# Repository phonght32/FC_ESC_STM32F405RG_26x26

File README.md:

# FC_ESC_STM32F405RG_26x26

### 1. Overview

All-in-One (AIO) circuit for quadcopter. STM32F405 is the main controller for FC and EFM8BB21 is the main controller for ESC. Screw hole dimension is 26x26 mm that compatible for almost tiny drone frame. 

Everything about this board: Schematic, PCB gerber and BOM are free to distribute under open-source license for users.

### 2. Specifications

| Items               | Specifications                                               |
| ------------------- | ------------------------------------------------------------ |
| Power supply        | Pin LiPo 2-4 cell                                            |
| Microcontroller     | STM32F405RGT6 / 32-bit ARM Cortex-M4 with FPU(168MHz, 225DMIPS) |
| Sensors             | MPU6000 (3 axis gyroscope, 3 axis accelerometer) <br />BMP280 (barometer)<br />INA186 (current) |
| Programmer          | JTAG/SWD connector                                           |
| Communicaton Ports  | UART x 4<br />I2C x 1<br />SPI x 1                           |
| OSD                 | Built-in AT7456                                              |
| LEDs and Buttons    | LED RED: 3V3 power on<br />LED BLUE: User status             |
| Output power source | TPS5430 5V@5A<br />RT9013 3V3@500mA                          |
| Dimensions          | 34 x34 mm<br />Screw hole 26 x 26 mm                         |

**NOTE:**

This board use jumper to select 5V power source and to enable 3V3 power supply.

### 3. Layout / Pin map

| Function    | Pin                                                          |
| ----------- | ------------------------------------------------------------ |
| UART1       | PA9: TX<br />PA10: RX                                        |
| UART3       | PB10: TX<br />PB11: RX                                       |
| UART4       | PA0: TX<br />PA1: RX                                         |
| UART6       | PC6: TX<br />PC7: RX                                         |
| SPI2        | PB12: CS<br />PB13: CLK<br />PB14: MISO<br />PB15: MOSI      |
| I2C2        | PB10: SCL<br />PB11: SDA                                     |
| LED         | LED status: PB7<br />LED strip: PB6                          |
| BUZZER      | PC13                                                         |
| USB Port    | D-: PA11<br />D+: PA12                                       |
| Measurement | Current sens: PC1<br />Voltage sens: PC2<br />USB voltage sens: PC5 |

### 4. Hardware design

#### Schematic

#### PCB F.Cu

#### PCB In1.Cu

#### PCB In2.Cu

#### PCB In3.Cu

#### PCB In4.Cu

#### PCB In5.Cu

#### PCB In6.Cu

#### PCB B.Cu

#### Dimension

#### 3D Top

#### 3D Bot

### 5. Bill of Materials (BOM)

[Download.](assets/BOM/FC_ESC_STM32F405RG_26x26.xlsx)

### 6. Gerber

[Download.](assets/gerber_FC_ESC_STM32F405RG_26x26_v1_0.zip)

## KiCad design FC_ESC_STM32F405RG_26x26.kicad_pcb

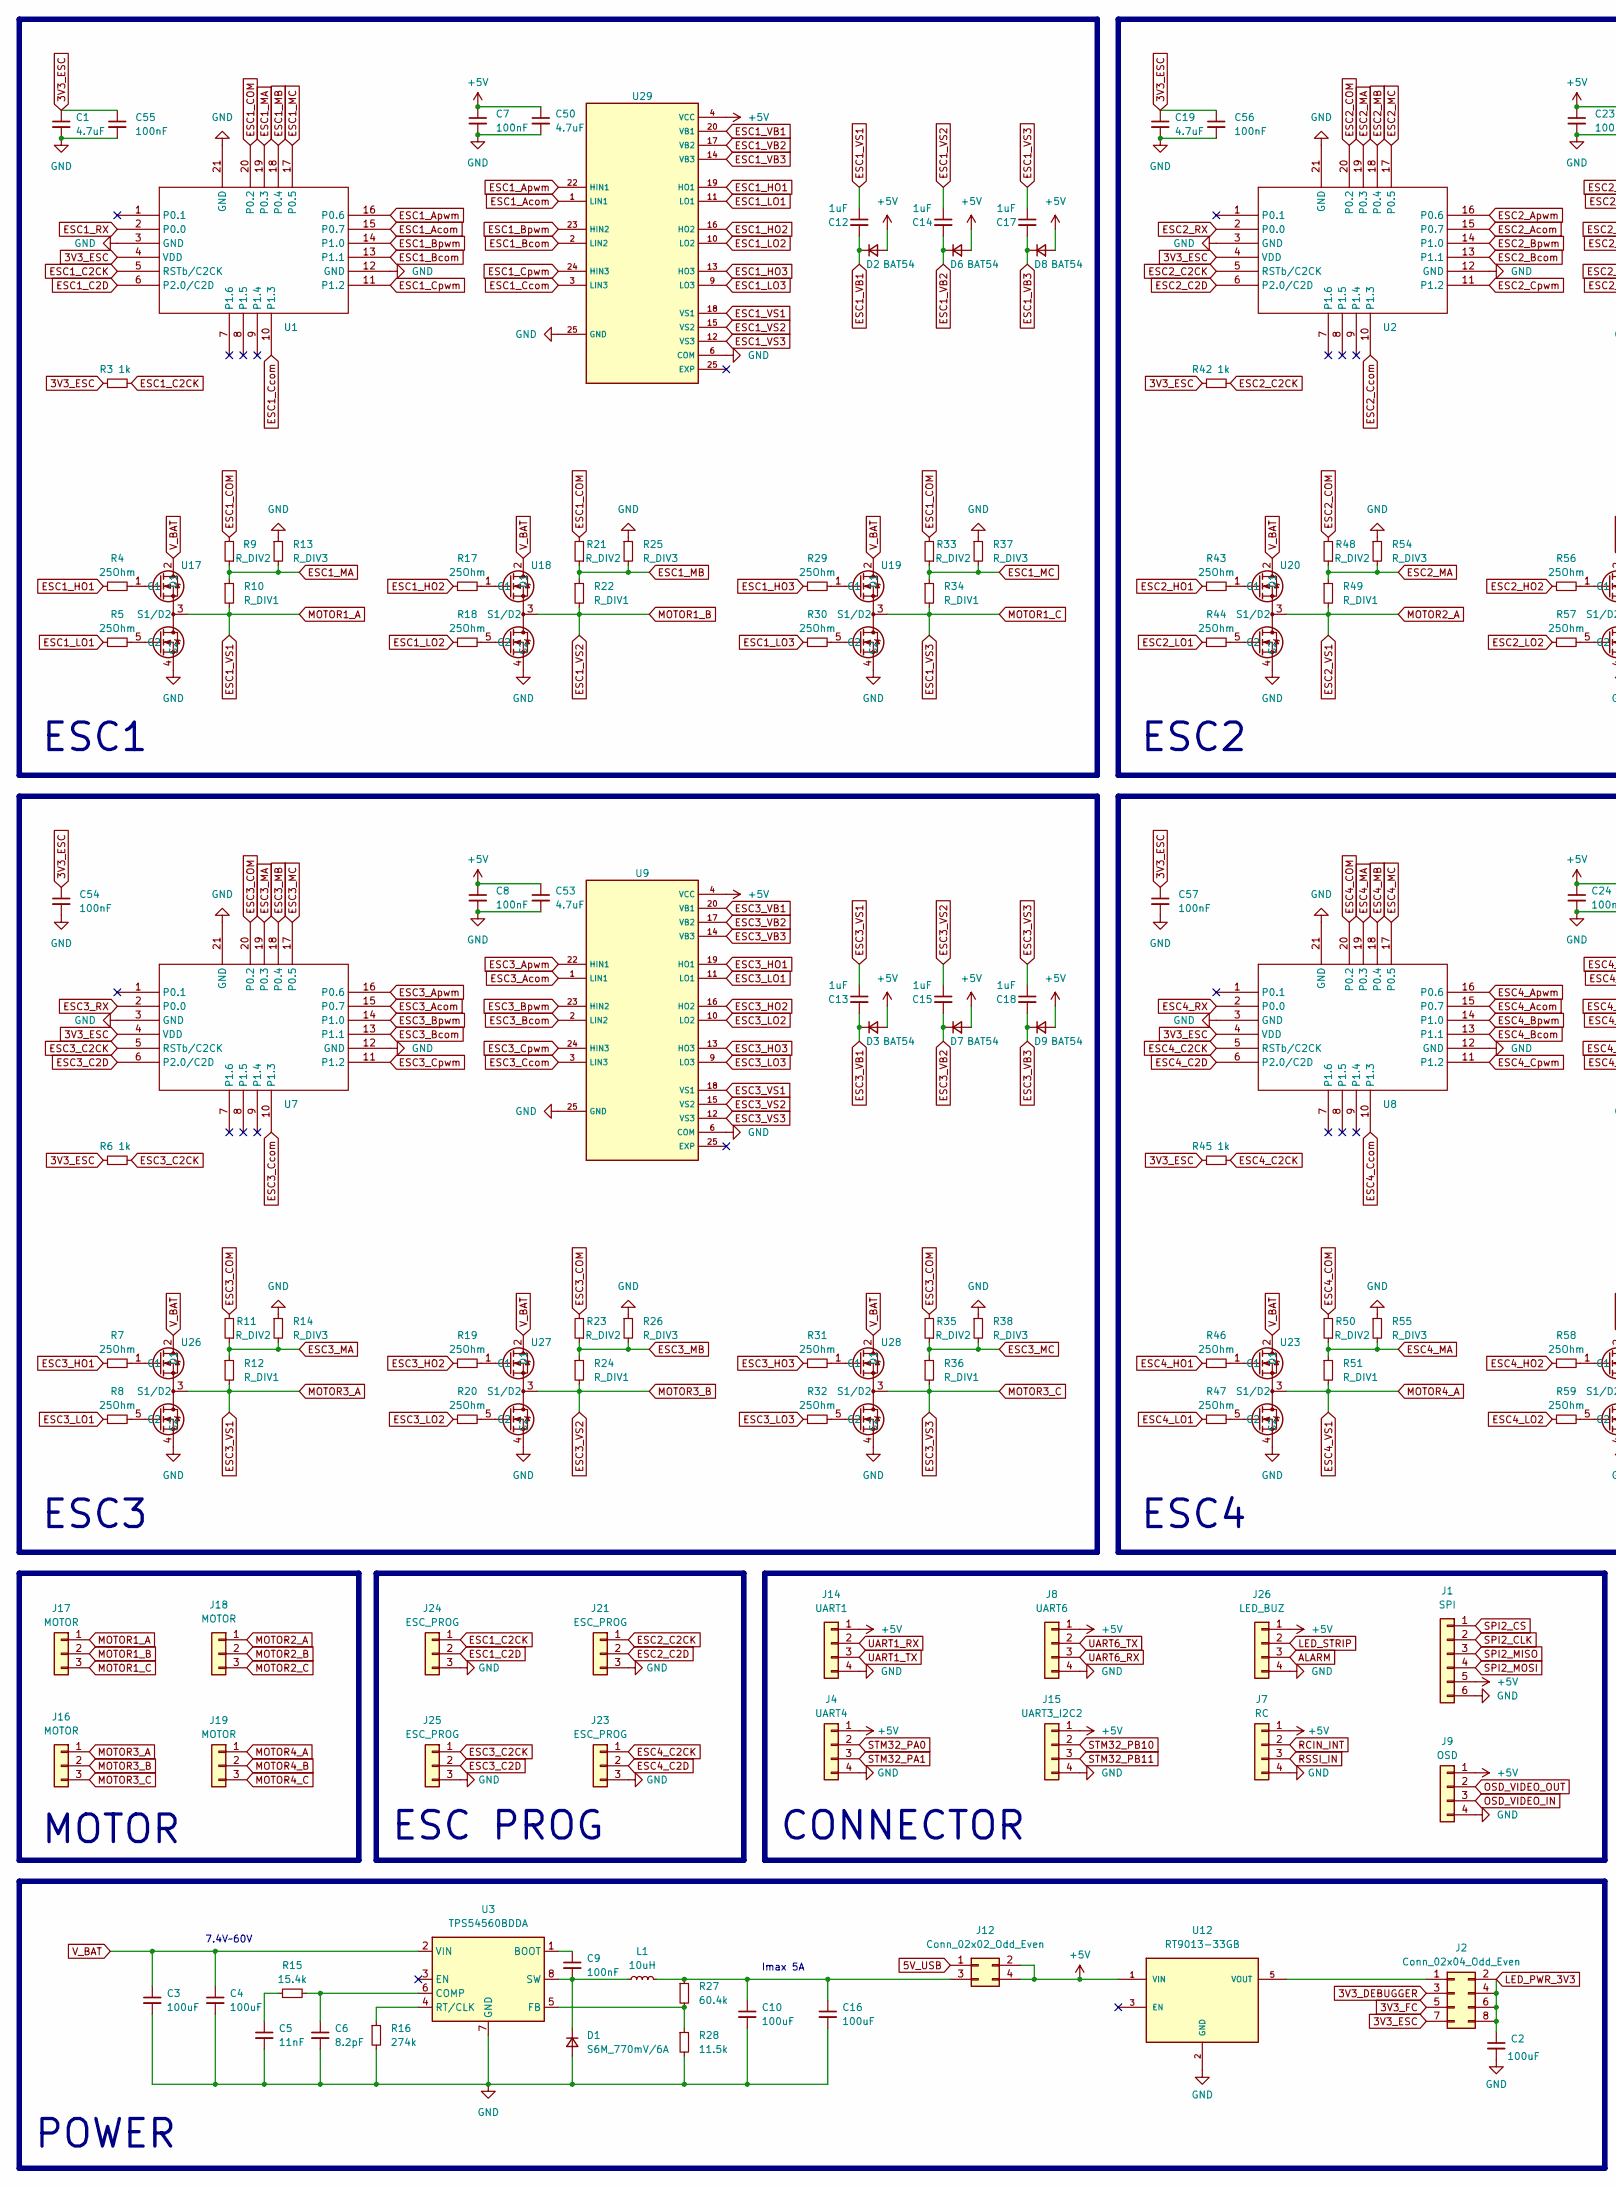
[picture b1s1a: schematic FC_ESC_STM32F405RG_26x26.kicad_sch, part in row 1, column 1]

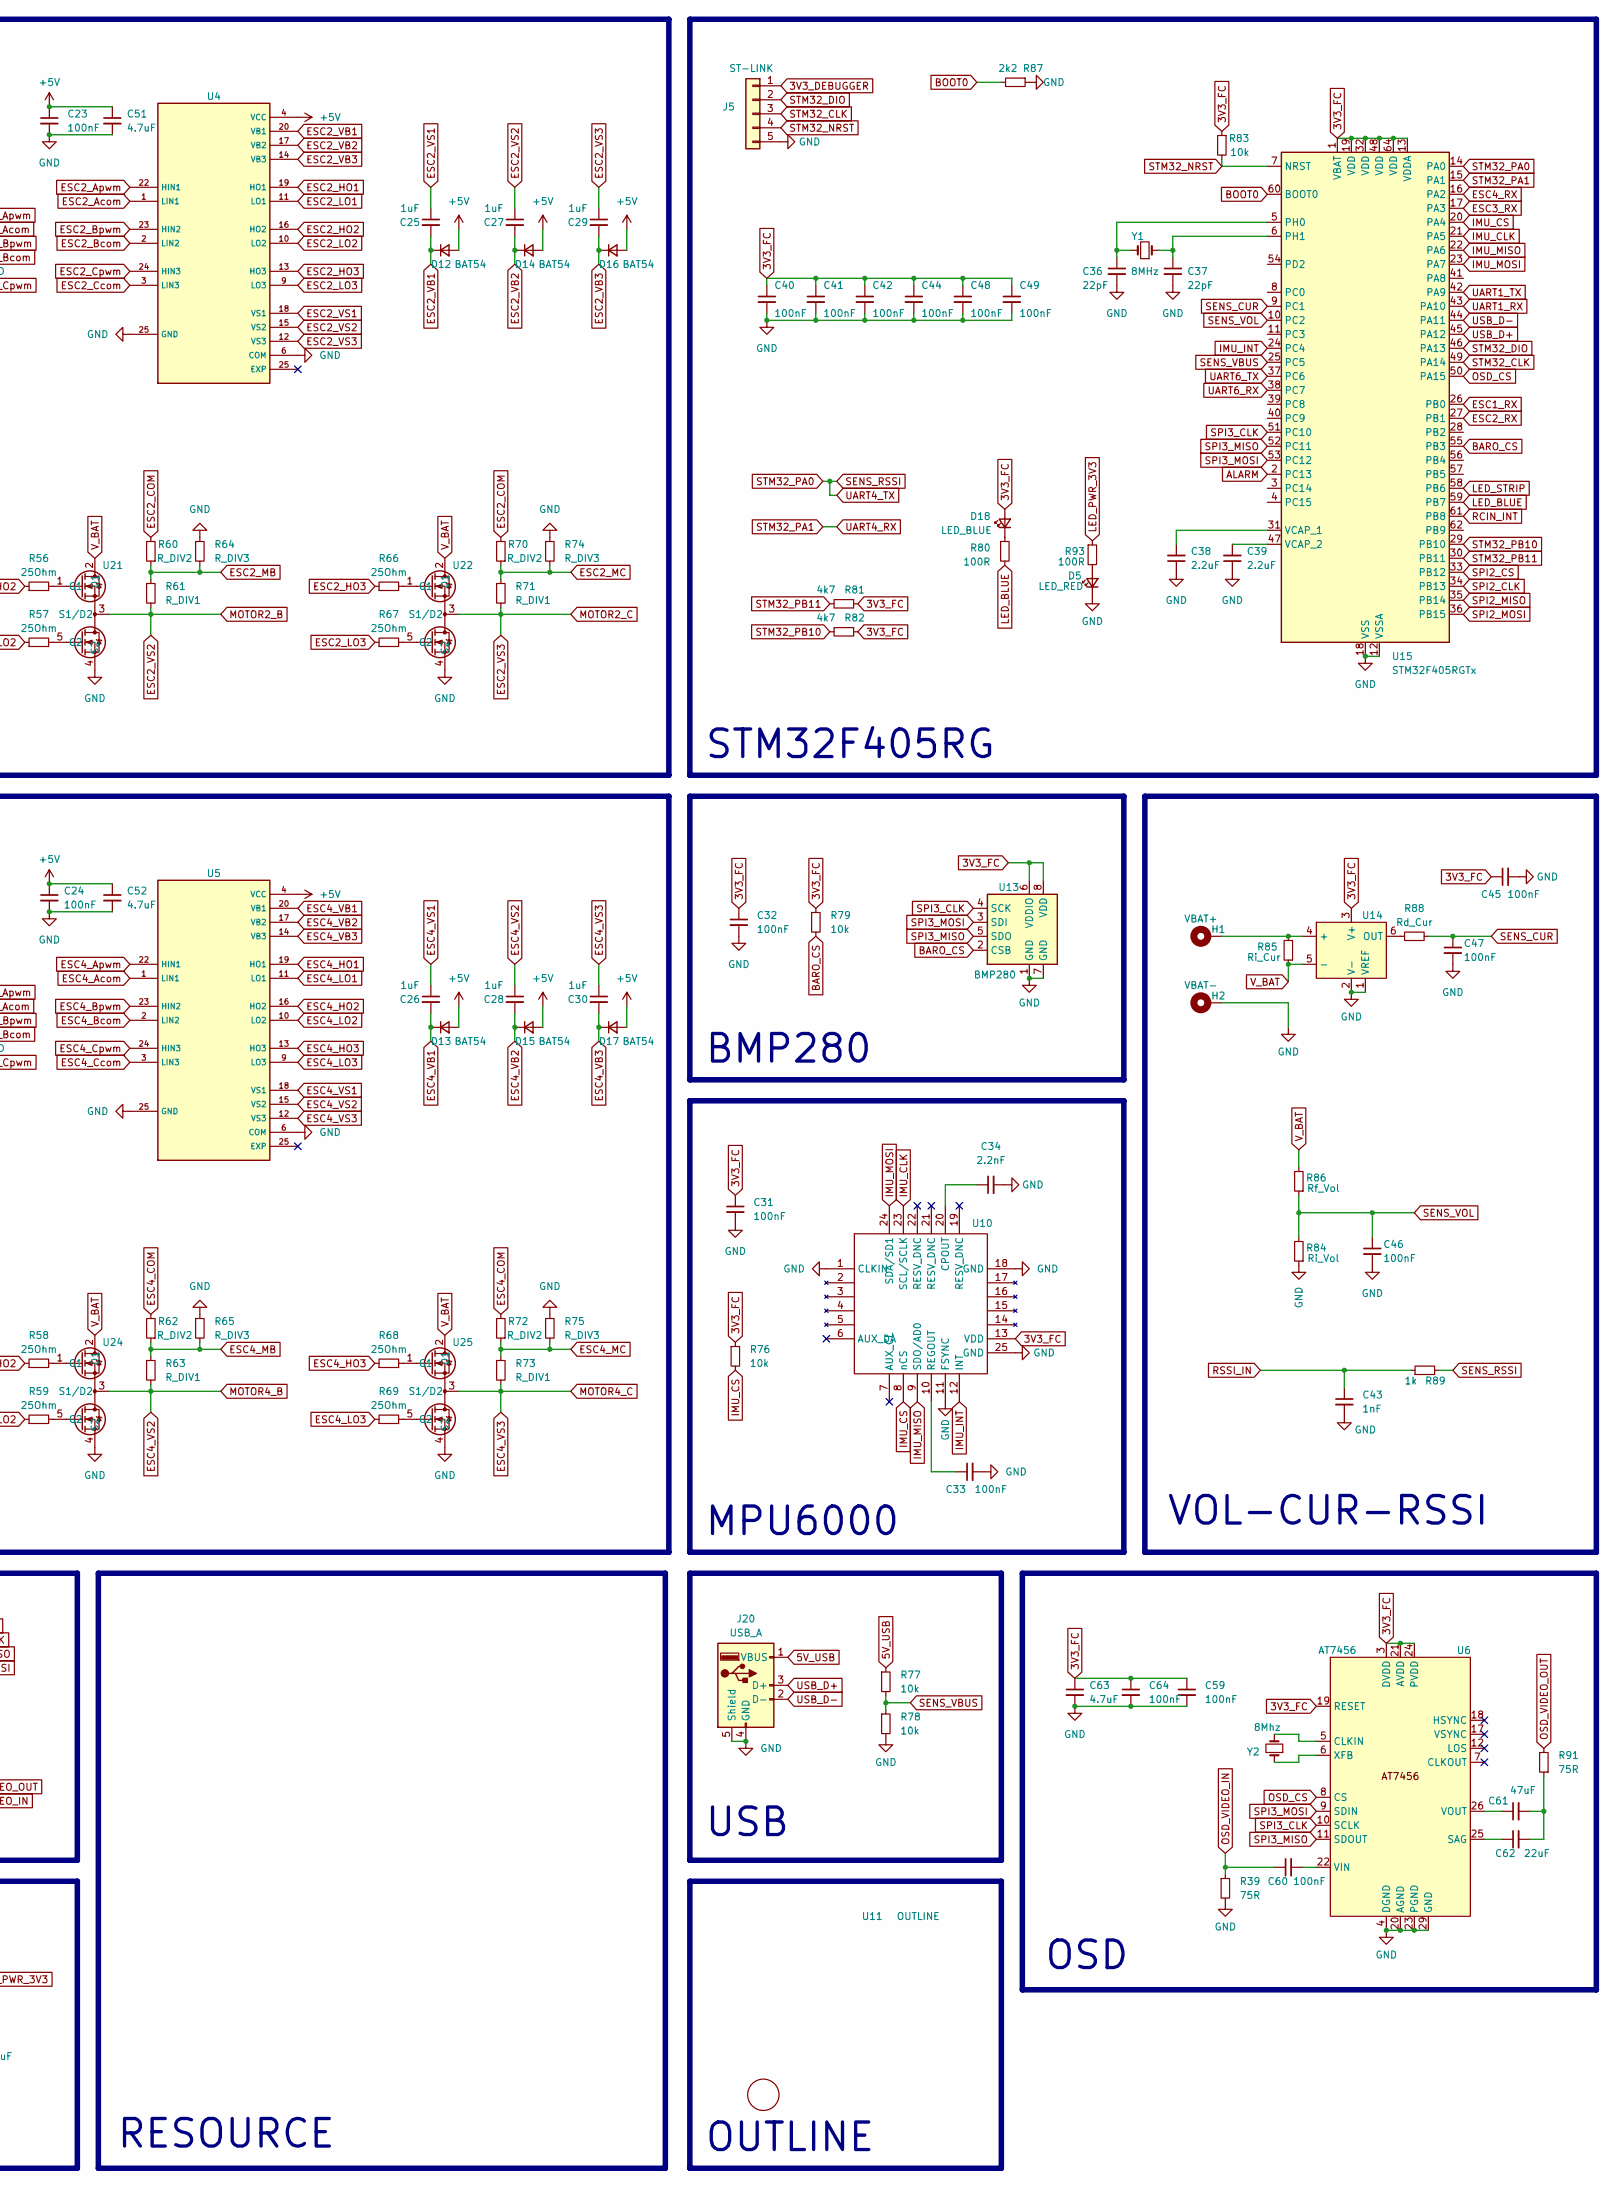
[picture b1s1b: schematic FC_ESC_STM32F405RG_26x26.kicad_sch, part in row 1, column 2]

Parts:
C1, C19: 4.7uF; C_1206_3216Metric_Pad1.33x1.80mm_HandSolder
C2, C3, C4, C10: 100uF; C_1210_3225Metric_Pad1.33x2.70mm_HandSolder
C5: 11nF; C_0402_1005Metric_Pad0.74x0.62mm_HandSolder
C6: 8.2pF; C_0402_1005Metric_Pad0.74x0.62mm_HandSolder
C7, C8, C9, C23, C24, C31, C32, C33, C40, C41, C42, C44, C45, C46, C47, C48, C49, C54, C55, C56, C57, C59, C60, C64: 100nF; C_0402_1005Metric_Pad0.74x0.62mm_HandSolder
C12, C13, C14, C15, C17, C18, C25, C26, C27, C28, C29, C30: 1uF; C_0402_1005Metric_Pad0.74x0.62mm_HandSolder
C16: 100uF; C_1206_3216Metric_Pad1.33x1.80mm_HandSolder
C34: 2.2nF; C_0402_1005Metric_Pad0.74x0.62mm_HandSolder
C36, C37: 22pF; C_0402_1005Metric_Pad0.74x0.62mm_HandSolder
C38, C39: 2.2uF; C_0402_1005Metric_Pad0.74x0.62mm_HandSolder
C43: 1nF; C_0402_1005Metric_Pad0.74x0.62mm_HandSolder
C50, C51, C52, C53: 4.7uF; C_0402_1005Metric_Pad0.74x0.62mm_HandSolder
C61: 47uF; C_0402_1005Metric_Pad0.74x0.62mm_HandSolder
C62: 22uF; C_0402_1005Metric_Pad0.74x0.62mm_HandSolder
C63: 4.7uF; C_0805_2012Metric_Pad1.18x1.45mm_HandSolder
D1: S6M_770mV/6A; D_SMA
D2, D3, D6, D7, D8, D9, D12, D13, D14, D15, D16, D17: BAT54; D_SOD-323
D5: LED_RED; LED_0402_1005Metric_Pad0.77x0.64mm_HandSolder
D18: LED_BLUE; LED_0402_1005Metric_Pad0.77x0.64mm_HandSolder
H1: VBAT+; MoutingPad
H2: VBAT-; MoutingPad
J1: SPI; MountingPad_1x6
J2: Conn_02x04_Odd_Even; PinHeader_2x04_P1.27mm_Vertical_SMD
J4: UART4; MountingPad_1x4
J5: ST-LINK; STLINK_Port
J7: RC; MountingPad_1x4
J8: UART6; MountingPad_1x4
J9: OSD; MountingPad_1x4
J12: Conn_02x02_Odd_Even; PinHeader_2x02_P1.27mm_Vertical_SMD
J14: UART1; MountingPad_1x4
J15: UART3_I2C2; MountingPad_1x4
J16, J17, J18, J19: MOTOR; Hirose_DF13-03P-1.25DS_1x03_P1.25mm_Horizontal
J20: USB_A; USB_Micro-B_SMD
J21, J23, J24, J25: ESC_PROG; ESC_Program
J26: LED_BUZ; MountingPad_1x4
L1: 10uH; Inductor
R3, R6, R42, R45, R89: 1k; R_0402_1005Metric_Pad0.72x0.64mm_HandSolder
R4, R5, R7, R8, R17, R18, R19, R20, R29, R30, R31, R32, R43, R44, R46, R47, R56, R57, R58, R59, R66, R67, R68, R69: 25Ohm; R_0402_1005Metric_Pad0.72x0.64mm_HandSolder
R9, R11, R21, R23, R33, R35, R48, R50, R60, R62, R70, R72: R_DIV2; R_0402_1005Metric_Pad0.72x0.64mm_HandSolder
R10, R12, R22, R24, R34, R36, R49, R51, R61, R63, R71, R73: R_DIV1; R_0402_1005Metric_Pad0.72x0.64mm_HandSolder
R13, R14, R25, R26, R37, R38, R54, R55, R64, R65, R74, R75: R_DIV3; R_0402_1005Metric_Pad0.72x0.64mm_HandSolder
R15: 15.4k; R_0402_1005Metric_Pad0.72x0.64mm_HandSolder
R16: 274k; R_0402_1005Metric_Pad0.72x0.64mm_HandSolder
R27: 60.4k; R_0402_1005Metric_Pad0.72x0.64mm_HandSolder
R28: 11.5k; R_0402_1005Metric_Pad0.72x0.64mm_HandSolder
R39, R91: 75R; R_0402_1005Metric_Pad0.72x0.64mm_HandSolder
R76, R77, R78, R79, R83: 10k; R_0402_1005Metric_Pad0.72x0.64mm_HandSolder
R80, R93: 100R; R_0402_1005Metric_Pad0.72x0.64mm_HandSolder
R81, R82: 4k7; R_0402_1005Metric_Pad0.72x0.64mm_HandSolder
R84: Ri_Vol; R_0402_1005Metric_Pad0.72x0.64mm_HandSolder
R85: Ri_Cur; R_2512_6332Metric
R86: Rf_Vol; R_0402_1005Metric_Pad0.72x0.64mm_HandSolder
R87: 2k2; R_0402_1005Metric_Pad0.72x0.64mm_HandSolder
R88: Rd_Cur; R_0402_1005Metric_Pad0.72x0.64mm_HandSolder
U1, U2, U7, U8: QFN-20-1EP_3x3mm_P0.5mm_EP1.8x1.8mm
U3: TPS54560BDDA; SOIC-8-1EP_3.9x4.9mm_P1.27mm_EP2.29x3mm
U4, U5, U9, U10, U29: QFN-24-1EP_4x4mm_P0.5mm_EP2.15x2.15mm
U6: AT7456; TSSOP-28-1EP_4.4x9.7mm_P0.65mm
U11: OUTLINE; Board_Outline
U12: RT9013-33GB; SOT65P210X110-6N; PARTREV Aprill 2011
U13: BMP280; Bosch_LGA-8_2x2.5mm_P0.65mm_ClockwisePinNumbering
U14: Texas_R-PDSO-G6
U15: STM32F405RGTx; LQFP-64_10x10mm_P0.5mm
U17, U18, U19, U20, U21, U22, U23, U24, U25, U26, U27, U28: SIZ200DT
Y1: 8MHz; Crystal_SMD_2016-4Pin_2.0x1.6mm
Y2: 8Mhz; Crystal_SMD_2016-4Pin_2.0x1.6mm

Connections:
3V3_DEBUGGER: J2.3, J5.1
3V3_ESC: C1.1, C19.1, C54.1, C55.1, C56.1, C57.1, J2.7, R3.1, R6.1, R42.1, R45.1, U1.4 (VDD), U2.4 (VDD), U7.4 (VDD), U8.4 (VDD)
3V3_FC: C31.1, C32.1, C40.1, C41.1, C42.1, C44.1, C45.1, C48.1, C49.1, C59.1, C63.1, C64.1, D18.2 (A), J2.5, R76.1, R79.1, R81.1, R82.1, R83.1, U6.3 (DVDD), U6.19 (RESET), U6.21 (AVDD), U6.24 (PVDD), U10.13 (VDD), U13.6 (VDDIO), U13.8 (VDD), U14.3 (V+), U15.1 (VBAT), U15.13 (VDDA), U15.19 (VDD), U15.32 (VDD), U15.48 (VDD), U15.64 (VDD)
5V_USB: J12.1, J20.1 (VBUS), R77.1
+5V: C7.1, C8.1, C23.1, C24.1, C50.1, C51.1, C52.1, C53.1, D2.2 (A), D3.2 (A), D6.2 (A), D7.2 (A), D8.2 (A), D9.2 (A), D12.2 (A), D13.2 (A), D14.2 (A), D15.2 (A), D16.2 (A), D17.2 (A), J1.5, J4.1, J7.1, J8.1, J9.1, J12.2, J12.4, J14.1, J15.1, J26.1, U4.4 (VCC), U5.4 (VCC), U9.4 (VCC), U12.1 (VIN), U29.4 (VCC)
ALARM: J26.3, U15.2 (PC13)
BARO_CS: R79.2, U13.2 (CSB), U15.55 (PB3)
BOOT0: R87.2, U15.60 (BOOT0)
ESC1_Acom: U1.15 (P0.7), U29.1 (LIN1)
ESC1_Apwm: U1.16 (P0.6), U29.22 (HIN1)
ESC1_Bcom: U1.13 (P1.1), U29.2 (LIN2)
ESC1_Bpwm: U1.14 (P1.0), U29.23 (HIN2)
ESC1_C2CK: J24.1, R3.2, U1.5 (RSTb/C2CK)
ESC1_C2D: J24.2, U1.6 (P2.0/C2D)
ESC1_COM: R9.2, R21.2, R33.2, U1.20 (P0.2)
ESC1_Ccom: U1.10 (P1.3), U29.3 (LIN3)
ESC1_Cpwm: U1.11 (P1.2), U29.24 (HIN3)
ESC1_HO1: R4.1, U29.19 (HO1)
ESC1_HO2: R17.1, U29.16 (HO2)
ESC1_HO3: R29.1, U29.13 (HO3)
ESC1_LO1: R5.1, U29.11 (LO1)
ESC1_LO2: R18.1, U29.10 (LO2)
ESC1_LO3: R30.1, U29.9 (LO3)
ESC1_MA: R9.1, R10.1, R13.2, U1.19 (P0.3)
ESC1_MB: R21.1, R22.1, R25.2, U1.18 (P0.4)
ESC1_MC: R33.1, R34.1, R37.2, U1.17 (P0.5)
ESC1_RX: U1.2 (P0.0), U15.26 (PB0)
ESC1_VB1: C12.2, D2.1 (K), U29.20 (VB1)
ESC1_VB2: C14.2, D6.1 (K), U29.17 (VB2)
ESC1_VB3: C17.2, D8.1 (K), U29.14 (VB3)
ESC1_VS1: C12.1, J17.1, R10.2, U17.3 (S1/D2), U29.18 (VS1)
ESC1_VS2: C14.1, J17.2, R22.2, U18.3 (S1/D2), U29.15 (VS2)
ESC1_VS3: C17.1, J17.3, R34.2, U19.3 (S1/D2), U29.12 (VS3)
ESC2_Acom: U2.15 (P0.7), U4.1 (LIN1)
ESC2_Apwm: U2.16 (P0.6), U4.22 (HIN1)
ESC2_Bcom: U2.13 (P1.1), U4.2 (LIN2)
ESC2_Bpwm: U2.14 (P1.0), U4.23 (HIN2)
ESC2_C2CK: J21.1, R42.2, U2.5 (RSTb/C2CK)
ESC2_C2D: J21.2, U2.6 (P2.0/C2D)
ESC2_COM: R48.2, R60.2, R70.2, U2.20 (P0.2)
ESC2_Ccom: U2.10 (P1.3), U4.3 (LIN3)
ESC2_Cpwm: U2.11 (P1.2), U4.24 (HIN3)
ESC2_HO1: R43.1, U4.19 (HO1)
ESC2_HO2: R56.1, U4.16 (HO2)
ESC2_HO3: R66.1, U4.13 (HO3)
ESC2_LO1: R44.1, U4.11 (LO1)
ESC2_LO2: R57.1, U4.10 (LO2)
ESC2_LO3: R67.1, U4.9 (LO3)
ESC2_MA: R48.1, R49.1, R54.2, U2.19 (P0.3)
ESC2_MB: R60.1, R61.1, R64.2, U2.18 (P0.4)
ESC2_MC: R70.1, R71.1, R74.2, U2.17 (P0.5)
ESC2_RX: U2.2 (P0.0), U15.27 (PB1)
ESC2_VB1: C25.2, D12.1 (K), U4.20 (VB1)
ESC2_VB2: C27.2, D14.1 (K), U4.17 (VB2)
ESC2_VB3: C29.2, D16.1 (K), U4.14 (VB3)
ESC2_VS1: C25.1, J18.1, R49.2, U4.18 (VS1), U20.3 (S1/D2)
ESC2_VS2: C27.1, J18.2, R61.2, U4.15 (VS2), U21.3 (S1/D2)
ESC2_VS3: C29.1, J18.3, R71.2, U4.12 (VS3), U22.3 (S1/D2)
ESC3_Acom: U7.15 (P0.7), U9.1 (LIN1)
ESC3_Apwm: U7.16 (P0.6), U9.22 (HIN1)
ESC3_Bcom: U7.13 (P1.1), U9.2 (LIN2)
ESC3_Bpwm: U7.14 (P1.0), U9.23 (HIN2)
ESC3_C2CK: J25.1, R6.2, U7.5 (RSTb/C2CK)
ESC3_C2D: J25.2, U7.6 (P2.0/C2D)
ESC3_COM: R11.2, R23.2, R35.2, U7.20 (P0.2)
ESC3_Ccom: U7.10 (P1.3), U9.3 (LIN3)
ESC3_Cpwm: U7.11 (P1.2), U9.24 (HIN3)
ESC3_HO1: R7.1, U9.19 (HO1)
ESC3_HO2: R19.1, U9.16 (HO2)
ESC3_HO3: R31.1, U9.13 (HO3)
ESC3_LO1: R8.1, U9.11 (LO1)
ESC3_LO2: R20.1, U9.10 (LO2)
ESC3_LO3: R32.1, U9.9 (LO3)
ESC3_MA: R11.1, R12.1, R14.2, U7.19 (P0.3)
ESC3_MB: R23.1, R24.1, R26.2, U7.18 (P0.4)
ESC3_MC: R35.1, R36.1, R38.2, U7.17 (P0.5)
ESC3_RX: U7.2 (P0.0), U15.17 (PA3)
ESC3_VB1: C13.2, D3.1 (K), U9.20 (VB1)
ESC3_VB2: C15.2, D7.1 (K), U9.17 (VB2)
ESC3_VB3: C18.2, D9.1 (K), U9.14 (VB3)
ESC3_VS1: C13.1, J16.1, R12.2, U9.18 (VS1), U26.3 (S1/D2)
ESC3_VS2: C15.1, J16.2, R24.2, U9.15 (VS2), U27.3 (S1/D2)
ESC3_VS3: C18.1, J16.3, R36.2, U9.12 (VS3), U28.3 (S1/D2)
ESC4_Acom: U5.1 (LIN1), U8.15 (P0.7)
ESC4_Apwm: U5.22 (HIN1), U8.16 (P0.6)
ESC4_Bcom: U5.2 (LIN2), U8.13 (P1.1)
ESC4_Bpwm: U5.23 (HIN2), U8.14 (P1.0)
ESC4_C2CK: J23.1, R45.2, U8.5 (RSTb/C2CK)
ESC4_C2D: J23.2, U8.6 (P2.0/C2D)
ESC4_COM: R50.2, R62.2, R72.2, U8.20 (P0.2)
ESC4_Ccom: U5.3 (LIN3), U8.10 (P1.3)
ESC4_Cpwm: U5.24 (HIN3), U8.11 (P1.2)
ESC4_HO1: R46.1, U5.19 (HO1)
ESC4_HO2: R58.1, U5.16 (HO2)
ESC4_HO3: R68.1, U5.13 (HO3)
ESC4_LO1: R47.1, U5.11 (LO1)
ESC4_LO2: R59.1, U5.10 (LO2)
ESC4_LO3: R69.1, U5.9 (LO3)
ESC4_MA: R50.1, R51.1, R55.2, U8.19 (P0.3)
ESC4_MB: R62.1, R63.1, R65.2, U8.18 (P0.4)
ESC4_MC: R72.1, R73.1, R75.2, U8.17 (P0.5)
ESC4_RX: U8.2 (P0.0), U15.16 (PA2)
ESC4_VB1: C26.2, D13.1 (K), U5.20 (VB1)
ESC4_VB2: C28.2, D15.1 (K), U5.17 (VB2)
ESC4_VB3: C30.2, D17.1 (K), U5.14 (VB3)
ESC4_VS1: C26.1, J19.1, R51.2, U5.18 (VS1), U23.3 (S1/D2)
ESC4_VS2: C28.1, J19.2, R63.2, U5.15 (VS2), U24.3 (S1/D2)
ESC4_VS3: C30.1, J19.3, R73.2, U5.12 (VS3), U25.3 (S1/D2)
GND: C1.2, C2.2, C3.2, C4.2, C5.2, C6.2, C7.2, C8.2, C10.2, C16.2, C19.2, C23.2, C24.2, C31.2, C32.2, C33.2, C34.2, C36.2, C37.2, C38.1, C39.1, C40.2, C41.2, C42.2, C43.2, C44.2, C45.2, C46.2, C47.2, C48.2, C49.2, C50.2, C51.2, C52.2, C53.2, C54.2, C55.2, C56.2, C57.2, C59.2, C63.2, C64.2, D1.2 (A), D5.1 (K), H2.1, J1.6, J4.4, J5.5, J7.4, J8.4, J9.4, J14.4, J15.4, J20.4 (GND), J20.5 (Shield), J21.3, J23.3, J24.3, J25.3, J26.4, R13.1, R14.1, R16.2, R25.1, R26.1, R28.2, R37.1, R38.1, R39.2, R54.1, R55.1, R64.1, R65.1, R74.1, R75.1, R78.2, R84.1, R87.1, U1.3 (GND), U1.12 (GND), U1.21 (GND), U2.3 (GND), U2.12 (GND), U2.21 (GND), U3.7 (GND), U3.9 (GND), U4.6 (COM), U4.25 (GND), U5.6 (COM), U5.25 (GND), U6.4 (DGND), U6.20 (AGND), U6.23 (PGND), U6.29 (GND), U7.3 (GND), U7.12 (GND), U7.21 (GND), U8.3 (GND), U8.12 (GND), U8.21 (GND), U9.6 (COM), U9.25 (GND), U10.1 (CLKIN), U10.11 (FSYNC), U10.18 (GND), U10.25 (GND), U12.2 (GND), U13.1 (GND), U13.7 (GND), U14.1 (VREF), U14.2 (V-), U15.12 (VSSA), U15.18 (VSS), U15.63 (VSS), U17.4 (S2), U18.4 (S2), U19.4 (S2), U20.4 (S2), U21.4 (S2), U22.4 (S2), U23.4 (S2), U24.4 (S2), U25.4 (S2), U26.4 (S2), U27.4 (S2), U28.4 (S2), U29.6 (COM), U29.25 (GND)
IMU_CLK: U10.23 (SCL/SCLK), U15.21 (PA5)
IMU_CS: R76.2, U10.8 (nCS), U15.20 (PA4)
IMU_INT: U10.12 (INT), U15.24 (PC4)
IMU_MISO: U10.9 (SDO/AD0), U15.22 (PA6)
IMU_MOSI: U10.24 (SDA/SD1), U15.23 (PA7)
LED_BLUE: R80.2, U15.59 (PB7)
LED_PWR_3V3: C2.1, J2.2, J2.4, J2.6, J2.8, R93.1
LED_STRIP: J26.2, U15.58 (PB6)
unnamed: C5.1, R15.1
unnamed: C61.2, C62.2, R91.1
unnamed: C9.2, D1.1 (K), L1.1, U3.8 (SW)
unnamed: D5.2 (A), R93.2
unnamed: D18.1 (K), R80.1
unnamed: J2.1, U12.5 (VOUT)
unnamed: C10.1, C16.1, J12.3, L1.2, R27.1
unnamed: C9.1, U3.1 (BOOT)
unnamed: C6.1, R15.2, U3.6 (COMP)
unnamed: R27.2, R28.1, U3.5 (FB)
unnamed: R16.1, U3.4 (RT/CLK)
unnamed: U6.5 (CLKIN), Y2.2
unnamed: C62.1, U6.25 (SAG)
unnamed: C60.2, U6.22 (VIN)
unnamed: C61.1, U6.26 (VOUT)
unnamed: U6.6 (XFB), Y2.1
unnamed: C34.1, U10.20 (CPOUT)
unnamed: C33.1, U10.10 (REGOUT)
unnamed: H1.1, R85.2, U14.4 (+)
unnamed: R88.1, U14.6 (OUT)
unnamed: C36.1, U15.5 (PH0), Y1.2
unnamed: C37.1, U15.6 (PH1), Y1.1
unnamed: C38.2, U15.31 (VCAP_1)
unnamed: C39.2, U15.47 (VCAP_2)
unnamed: R4.2, U17.1 (G1)
unnamed: R5.2, U17.5 (G2)
unnamed: R17.2, U18.1 (G1)
unnamed: R18.2, U18.5 (G2)
unnamed: R29.2, U19.1 (G1)
unnamed: R30.2, U19.5 (G2)
unnamed: R43.2, U20.1 (G1)
unnamed: R44.2, U20.5 (G2)
unnamed: R56.2, U21.1 (G1)
unnamed: R57.2, U21.5 (G2)
unnamed: R66.2, U22.1 (G1)
unnamed: R67.2, U22.5 (G2)
unnamed: R46.2, U23.1 (G1)
unnamed: R47.2, U23.5 (G2)
unnamed: R58.2, U24.1 (G1)
unnamed: R59.2, U24.5 (G2)
unnamed: R68.2, U25.1 (G1)
unnamed: R69.2, U25.5 (G2)
unnamed: R7.2, U26.1 (G1)
unnamed: R8.2, U26.5 (G2)
unnamed: R19.2, U27.1 (G1)
unnamed: R20.2, U27.5 (G2)
unnamed: R31.2, U28.1 (G1)
unnamed: R32.2, U28.5 (G2)
OSD_CS: U6.8 (CS), U15.50 (PA15)
OSD_VIDEO_IN: C60.1, J9.3, R39.1
OSD_VIDEO_OUT: J9.2, R91.2
RCIN_INT: J7.2, U15.61 (PB8)
RSSI_IN: C43.1, J7.3, R89.1
SENS_CUR: C47.1, R88.2, U15.9 (PC1)
SENS_RSSI: J4.2, R89.2, U15.14 (PA0)
SENS_VBUS: R77.2, R78.1, U15.25 (PC5)
SENS_VOL: C46.1, R84.2, R86.1, U15.10 (PC2)
SPI2_CLK: J1.2, U15.34 (PB13)
SPI2_CS: J1.1, U15.33 (PB12)
SPI2_MISO: J1.3, U15.35 (PB14)
SPI2_MOSI: J1.4, U15.36 (PB15)
SPI3_CLK: U6.10 (SCLK), U13.4 (SCK), U15.51 (PC10)
SPI3_MISO: U6.11 (SDOUT), U13.5 (SDO), U15.52 (PC11)
SPI3_MOSI: U6.9 (SDIN), U13.3 (SDI), U15.53 (PC12)
STM32_CLK: J5.3, U15.49 (PA14)
STM32_DIO: J5.2, U15.46 (PA13)
STM32_NRST: J5.4, R83.2, U15.7 (NRST)
STM32_PA1: J4.3, U15.15 (PA1)
STM32_PB10: J15.2, R82.2, U15.29 (PB10)
STM32_PB11: J15.3, R81.2, U15.30 (PB11)
UART1_RX: J14.2, U15.43 (PA10)
UART1_TX: J14.3, U15.42 (PA9)
UART6_RX: J8.3, U15.38 (PC7)
UART6_TX: J8.2, U15.37 (PC6)
USB_D+: J20.3 (D+), U15.45 (PA12)
USB_D-: J20.2 (D-), U15.44 (PA11)
V_BAT: C3.1, C4.1, R85.1, R86.2, U3.2 (VIN), U14.5 (-), U17.2 (D1), U18.2 (D1), U19.2 (D1), U20.2 (D1), U21.2 (D1), U22.2 (D1), U23.2 (D1), U24.2 (D1), U25.2 (D1), U26.2 (D1), U27.2 (D1), U28.2 (D1)

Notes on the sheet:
VOL-CUR-RSSI
ESC1
BMP280
ESC4
RESOURCE
CONNECTOR
7.4V~60V
ESC PROG
MPU6000
MOTOR
ESC3
Imax 5A
ESC2
OUTLINE
POWER
OSD
USB
STM32F405RG

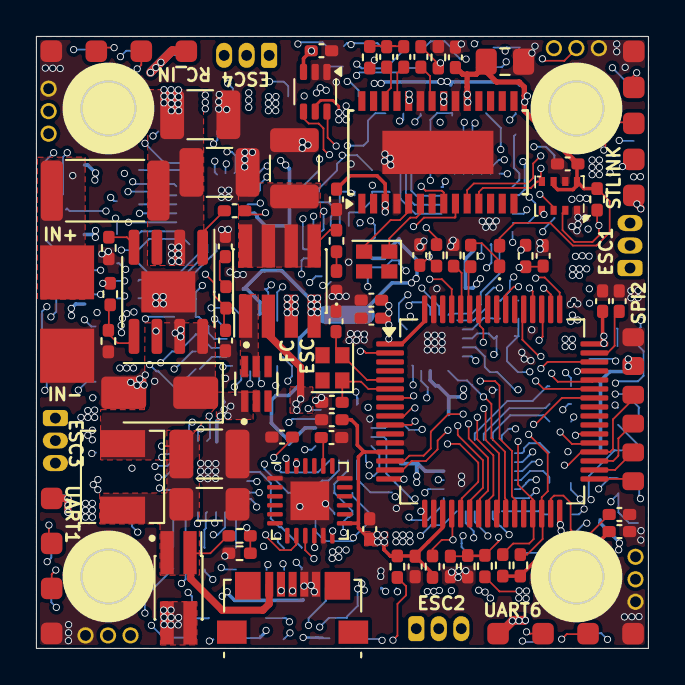
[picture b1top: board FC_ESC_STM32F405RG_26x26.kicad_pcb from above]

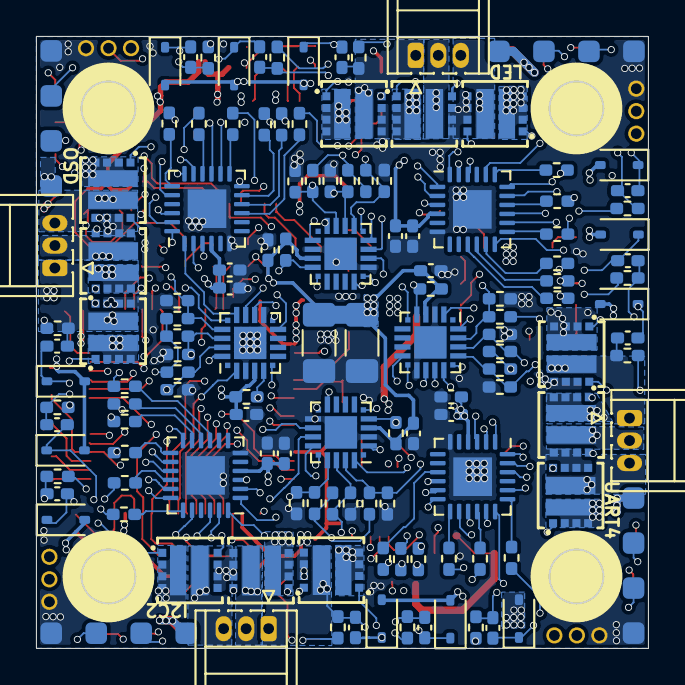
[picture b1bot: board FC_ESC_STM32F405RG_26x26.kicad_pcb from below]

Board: 8 copper layers, 34.0 x 34.0 mm, 211 parts (130 on the bottom side), 194 nets.

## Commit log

2023-10-15 add ESC and STM32F405RG
2023-10-18 update project
2023-10-20 update current-voltage measure
2023-10-21 update pcb
2023-10-22 update placement
2023-12-05 update library
2023-12-10 update schematic
2023-12-10 update demo
2023-12-11 update routing
2024-01-02 complete routing
2024-01-06 add dimension
2024-03-02 upgrade to Kicad v8
2024-03-02 update setting for export BOM
2024-03-02 add BOM
2024-03-02 add BOM download link
2024-03-02 update 3d model
2024-03-02 add gerver v1.0
2024-03-02 add download gerber
2024-03-02 change origin
2024-03-02 add symbol value
2024-03-02 update BOM
2024-03-02 update symbol value
